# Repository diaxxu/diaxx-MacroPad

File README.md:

# Diaxx’s Macropad

Hi! This is my submission for Hackpad.  
It’s a small 9-key macropad built around the Seeed XIAO RP2040, with a rotary encoder and RGB lighting.  
I wanted it to be simple and aesthetic ^^

---

## Features
- mechanical MX-style keys  
- EC11 rotary encoder   
- SK6812 Mini-E RGB LEDs  
- PCB designed in KiCad  
- 3D printed case made in Fusion 360  
- KMK firmware   
- Designed it for my own preferences ( shortcuts etc...) 

---

## PCB
The PCB was made entirely in KiCad. Everything passes ERC.  

**PCB Layout:**  

edit : Looking at it again, I can’t believe I actually made something like this.

**Schematic:**  

---

## CAD
The case is modeled in Fusion 360.  
It’s a two-part design (top + bottom) using m3 self tapping screws to hold everything together. ( or hot glue... ) 

The full assembly is included as a `.STEP` file in the CAD folder.

---

## Firmware
The firmware uses **KMK**, running on CircuitPython.  
`main.py` 

---

## Notes
I’m still new to KiCad and electronics, so making this board taught me a lot. 
Routing the traces, assigning footprints and spacing everything correctly took some trial and error, but the final design came together nicely and i learnt so much !!! 
also i want to thank hackclub because this is the first time someone gave me an opportunity in my life to do what i love .

---

## BOM
- 1× Seeed XIAO RP2040  
- 9× MX-style switches
- 9x Blank DSA Keycaps ( white please <3 ) 
- 9× 1N4148 diodes  
- 1× EC11 rotary encoder  +  Knob
- 4× SK6812 Mini-E LEDs  
- 4× M3 self-taping screws ( i will buy them myself since they are pretty cheap )   
- 3D printed case (top + bottom) both black so they could go with the white keycap.

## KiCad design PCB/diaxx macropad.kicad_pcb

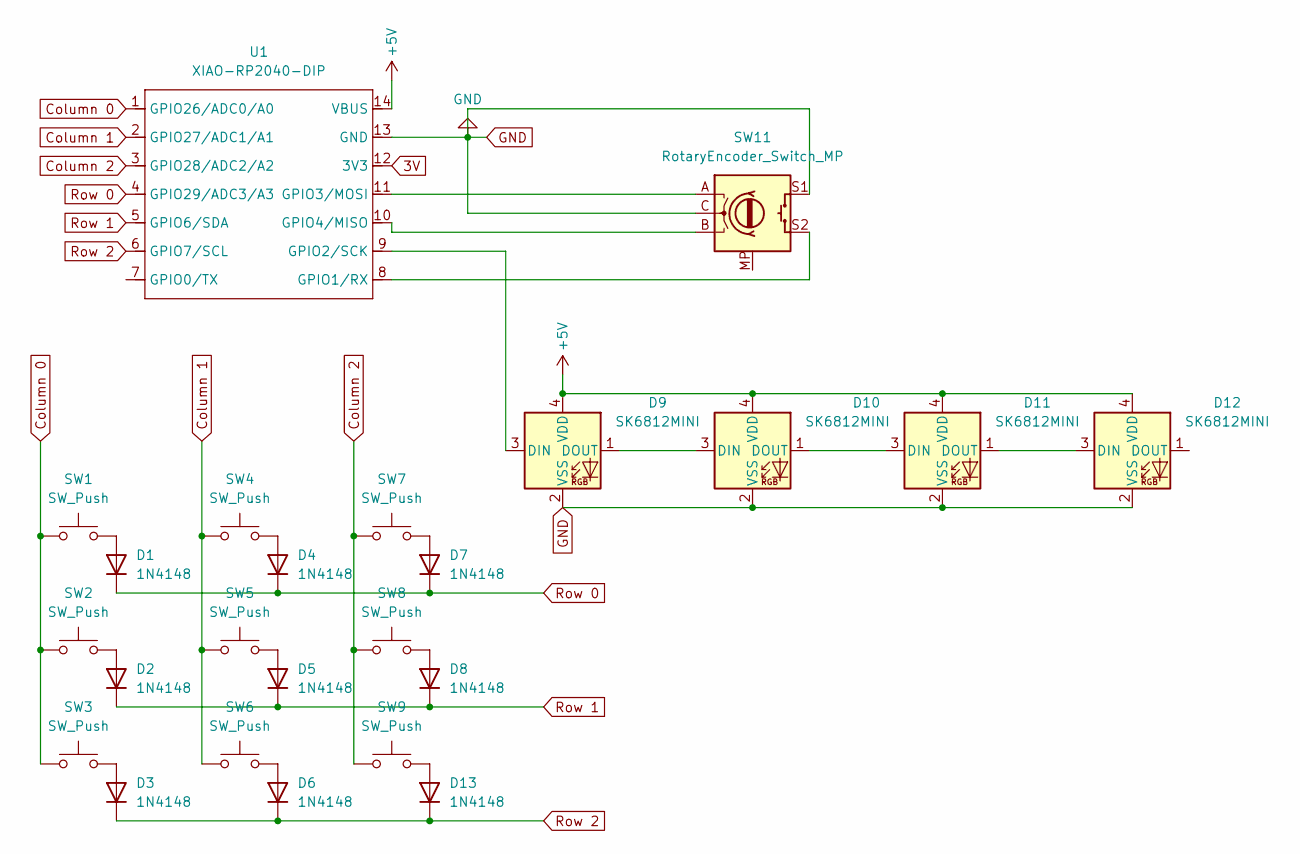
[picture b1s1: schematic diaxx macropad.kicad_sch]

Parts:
D1, D2, D3, D4, D5, D6, D7, D8, D13: 1N4148; D_DO-35_SOD27_P7.62mm_Horizontal
D9, D10, D11, D12: SK6812MINI; LED_SK6812MINI_PLCC4_3.5x3.5mm_P1.75mm
SW1, SW2, SW3, SW4, SW5, SW6, SW7, SW8, SW9: SW_Push; SW_Cherry_MX_1.00u_PCB
SW11: RotaryEncoder_Switch_MP; RotaryEncoder_Alps_EC11E-Switch_Vertical_H20mm
U1: XIAO-RP2040-DIP

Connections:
3V: U1.12 (3V3)
+5V: D9.4 (VDD), D10.4 (VDD), D11.4 (VDD), D12.4 (VDD), U1.14 (VBUS)
Column 0: SW1.1, SW2.1, SW3.1, U1.1 (GPIO26/ADC0/A0)
Column 1: SW4.1, SW5.1, SW6.1, U1.2 (GPIO27/ADC1/A1)
Column 2: SW7.1, SW8.1, SW9.1, U1.3 (GPIO28/ADC2/A2)
GND: D9.2 (VSS), D10.2 (VSS), D11.2 (VSS), D12.2 (VSS), SW11.C, SW11.S1, U1.13 (GND)
unnamed: D1.2 (A), SW1.2
unnamed: D2.2 (A), SW2.2
unnamed: D3.2 (A), SW3.2
unnamed: D4.2 (A), SW4.2
unnamed: D5.2 (A), SW5.2
unnamed: D6.2 (A), SW6.2
unnamed: D7.2 (A), SW7.2
unnamed: D8.2 (A), SW8.2
unnamed: D9.3 (DIN), U1.9 (GPIO2/SCK)
unnamed: D9.1 (DOUT), D10.3 (DIN)
unnamed: D10.1 (DOUT), D11.3 (DIN)
unnamed: D11.1 (DOUT), D12.3 (DIN)
unnamed: D13.2 (A), SW9.2
unnamed: SW11.S2, U1.8 (GPIO1/RX)
unnamed: SW11.A, U1.11 (GPIO3/MOSI)
unnamed: SW11.B, U1.10 (GPIO4/MISO)
Row 0: D1.1 (K), D4.1 (K), D7.1 (K), U1.4 (GPIO29/ADC3/A3)
Row 1: D2.1 (K), D5.1 (K), D8.1 (K), U1.5 (GPIO6/SDA)
Row 2: D3.1 (K), D6.1 (K), D13.1 (K), U1.6 (GPIO7/SCL)

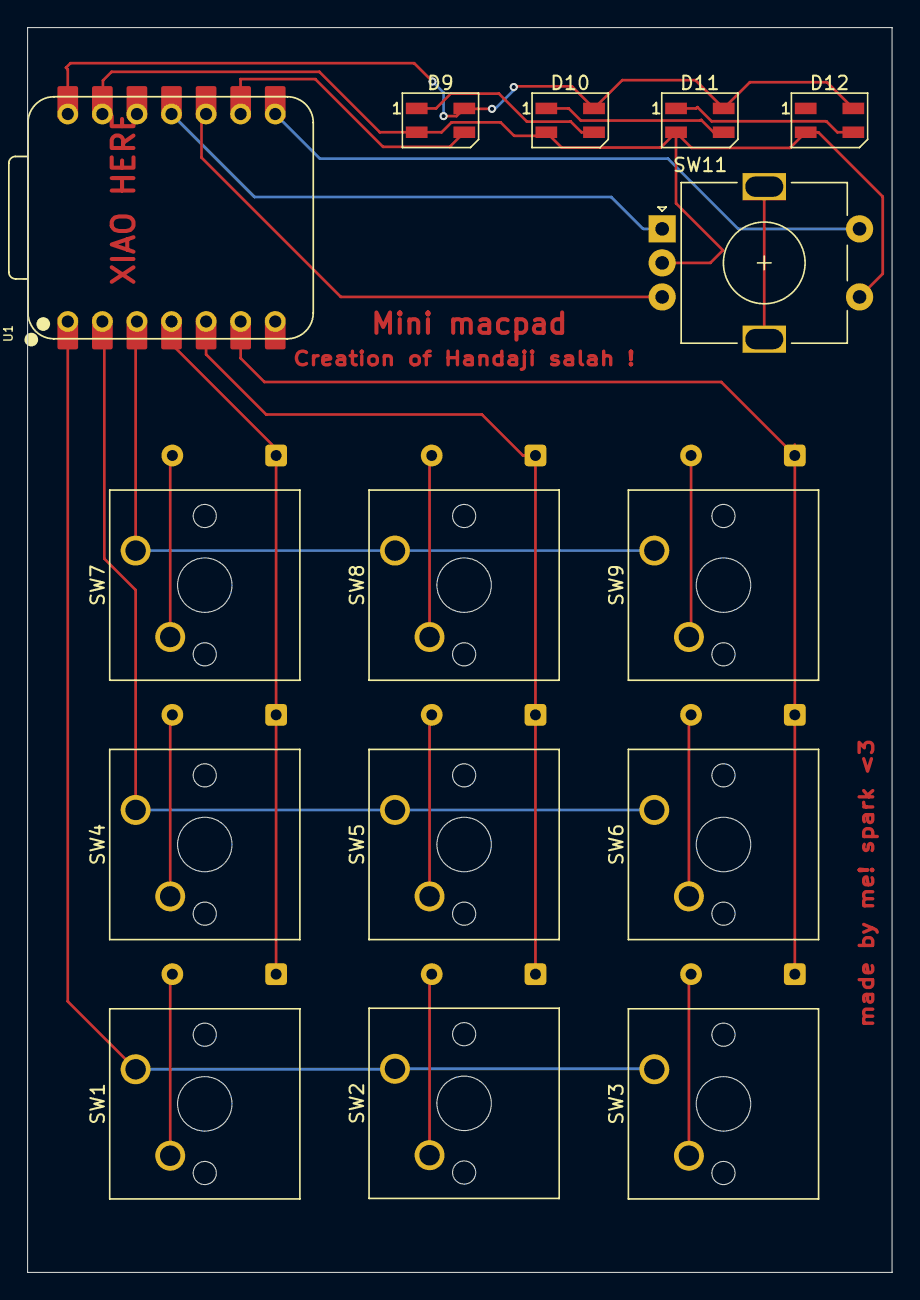
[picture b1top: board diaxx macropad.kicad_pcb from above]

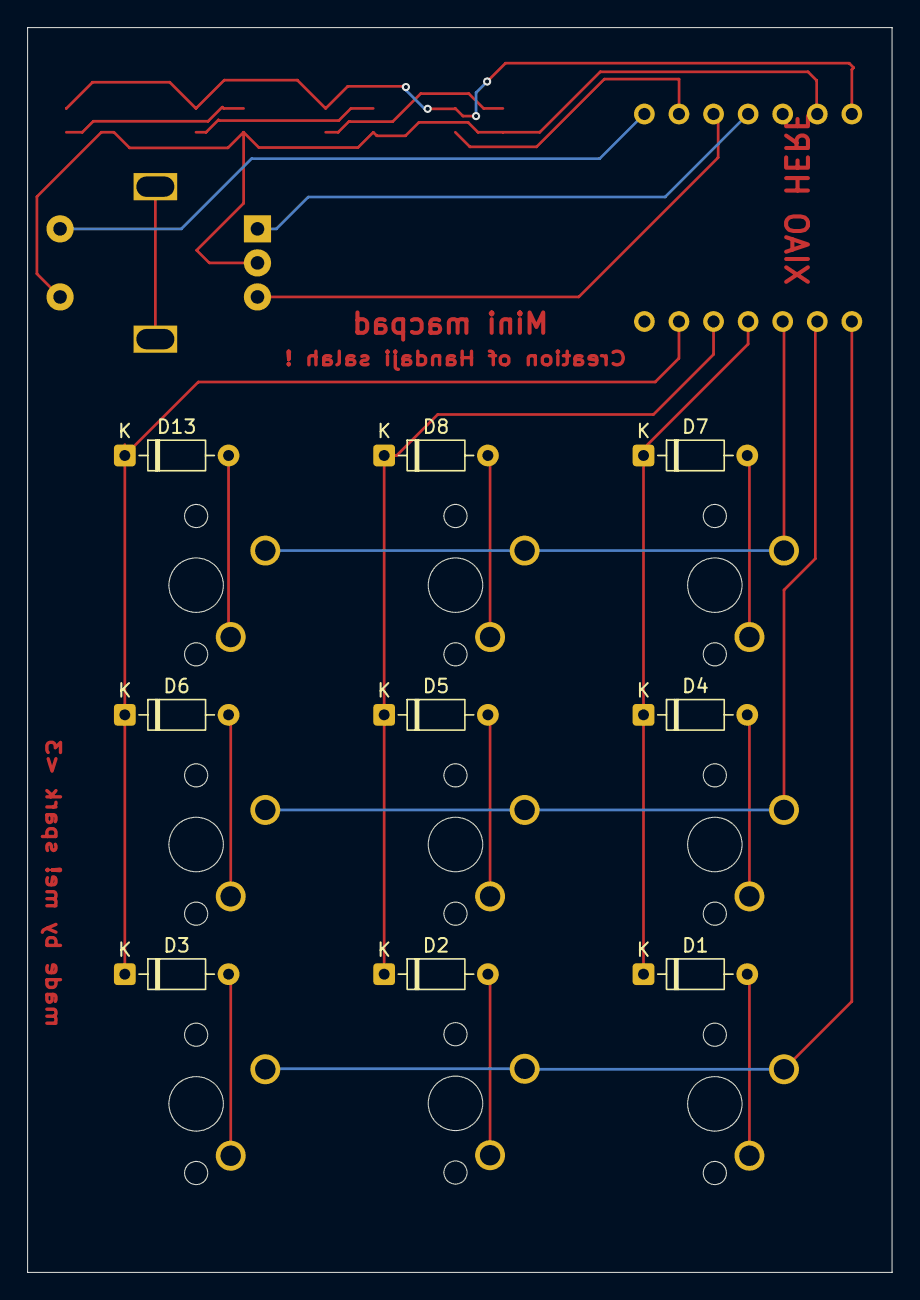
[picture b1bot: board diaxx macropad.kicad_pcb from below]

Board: 2 copper layers, 63.5 x 91.4 mm, 24 parts (9 on the bottom side), 24 nets.

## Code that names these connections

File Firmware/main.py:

from kmk.kmk_keyboard import KMKKeyboard
from kmk.scanners.keypad import MatrixScanner
from kmk.keys import KC
from kmk.modules.encoder import EncoderHandler
from kmk.modules.neo_pixel import Neopixel

keyboard = KMKKeyboard()

# ---------------------------
# MATRIX CONFIGURATION
# ---------------------------


# Columns: 26, 27, 28
# Rows:    29, 6, 7

keyboard.col_pins = (26, 27, 28)
keyboard.row_pins = (29, 6, 7)


keyboard.diode_orientation = keyboard.DIODE_COL2ROW

# ---------------------------
# ROTARY ENCODER
# ---------------------------

encoders = EncoderHandler()
keyboard.modules.append(encoders)

# Encoder A = GPIO3
# Encoder B = GPIO4
# Press switch = GPIO1

encoders.pins = (
    (3, 4),   # (A, B)
)

encoders.map = [
    ( (KC.VOLU, KC.VOLD), )   # clockwise → volume up, ccw → volume down
]

# Encoder push button
ENCODER_PRESS = KC.ENT  
keyboard.hotkey = {(1,): ENCODER_PRESS}

# ---------------------------
# RGB LED STRIP (SK6812 MINI)
# ---------------------------

# 4 LEDs on GPIO2
rgb = Neopixel(
    pin=2,
    num_pixels=4,
    brightness=0.4,
    pixel_order=Neopixel.GRB
)
keyboard.modules.append(rgb)

# ---------------------------
# KEYMAP
# ---------------------------




keyboard.keymap = [
    [
        KC.A, KC.B, KC.C,   # row 0
        KC.D, KC.NO, KC.NO, # row 1
        KC.NO, KC.NO, KC.NO # row 2
    ]
]

# ---------------------------
# START
# ---------------------------

if __name__ == '__main__':
    keyboard.go()

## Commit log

2025-12-05 Rename Capture d'écran 2025-12-04 220606.png to image_1
2025-12-05 Rename Capture d'écran 2025-12-05 010740.png to cad12
2025-12-05 Set up keyboard with matrix, encoder, and RGB LED
    Initialize keyboard configuration with matrix, encoder, and RGB LED settings.
2025-12-05 Refactor main.py for cleaner structure
2025-12-05 Refactor main.py for cleaner code structure
2025-12-05 Update screw description from 'self insert' to 'self tapping'
